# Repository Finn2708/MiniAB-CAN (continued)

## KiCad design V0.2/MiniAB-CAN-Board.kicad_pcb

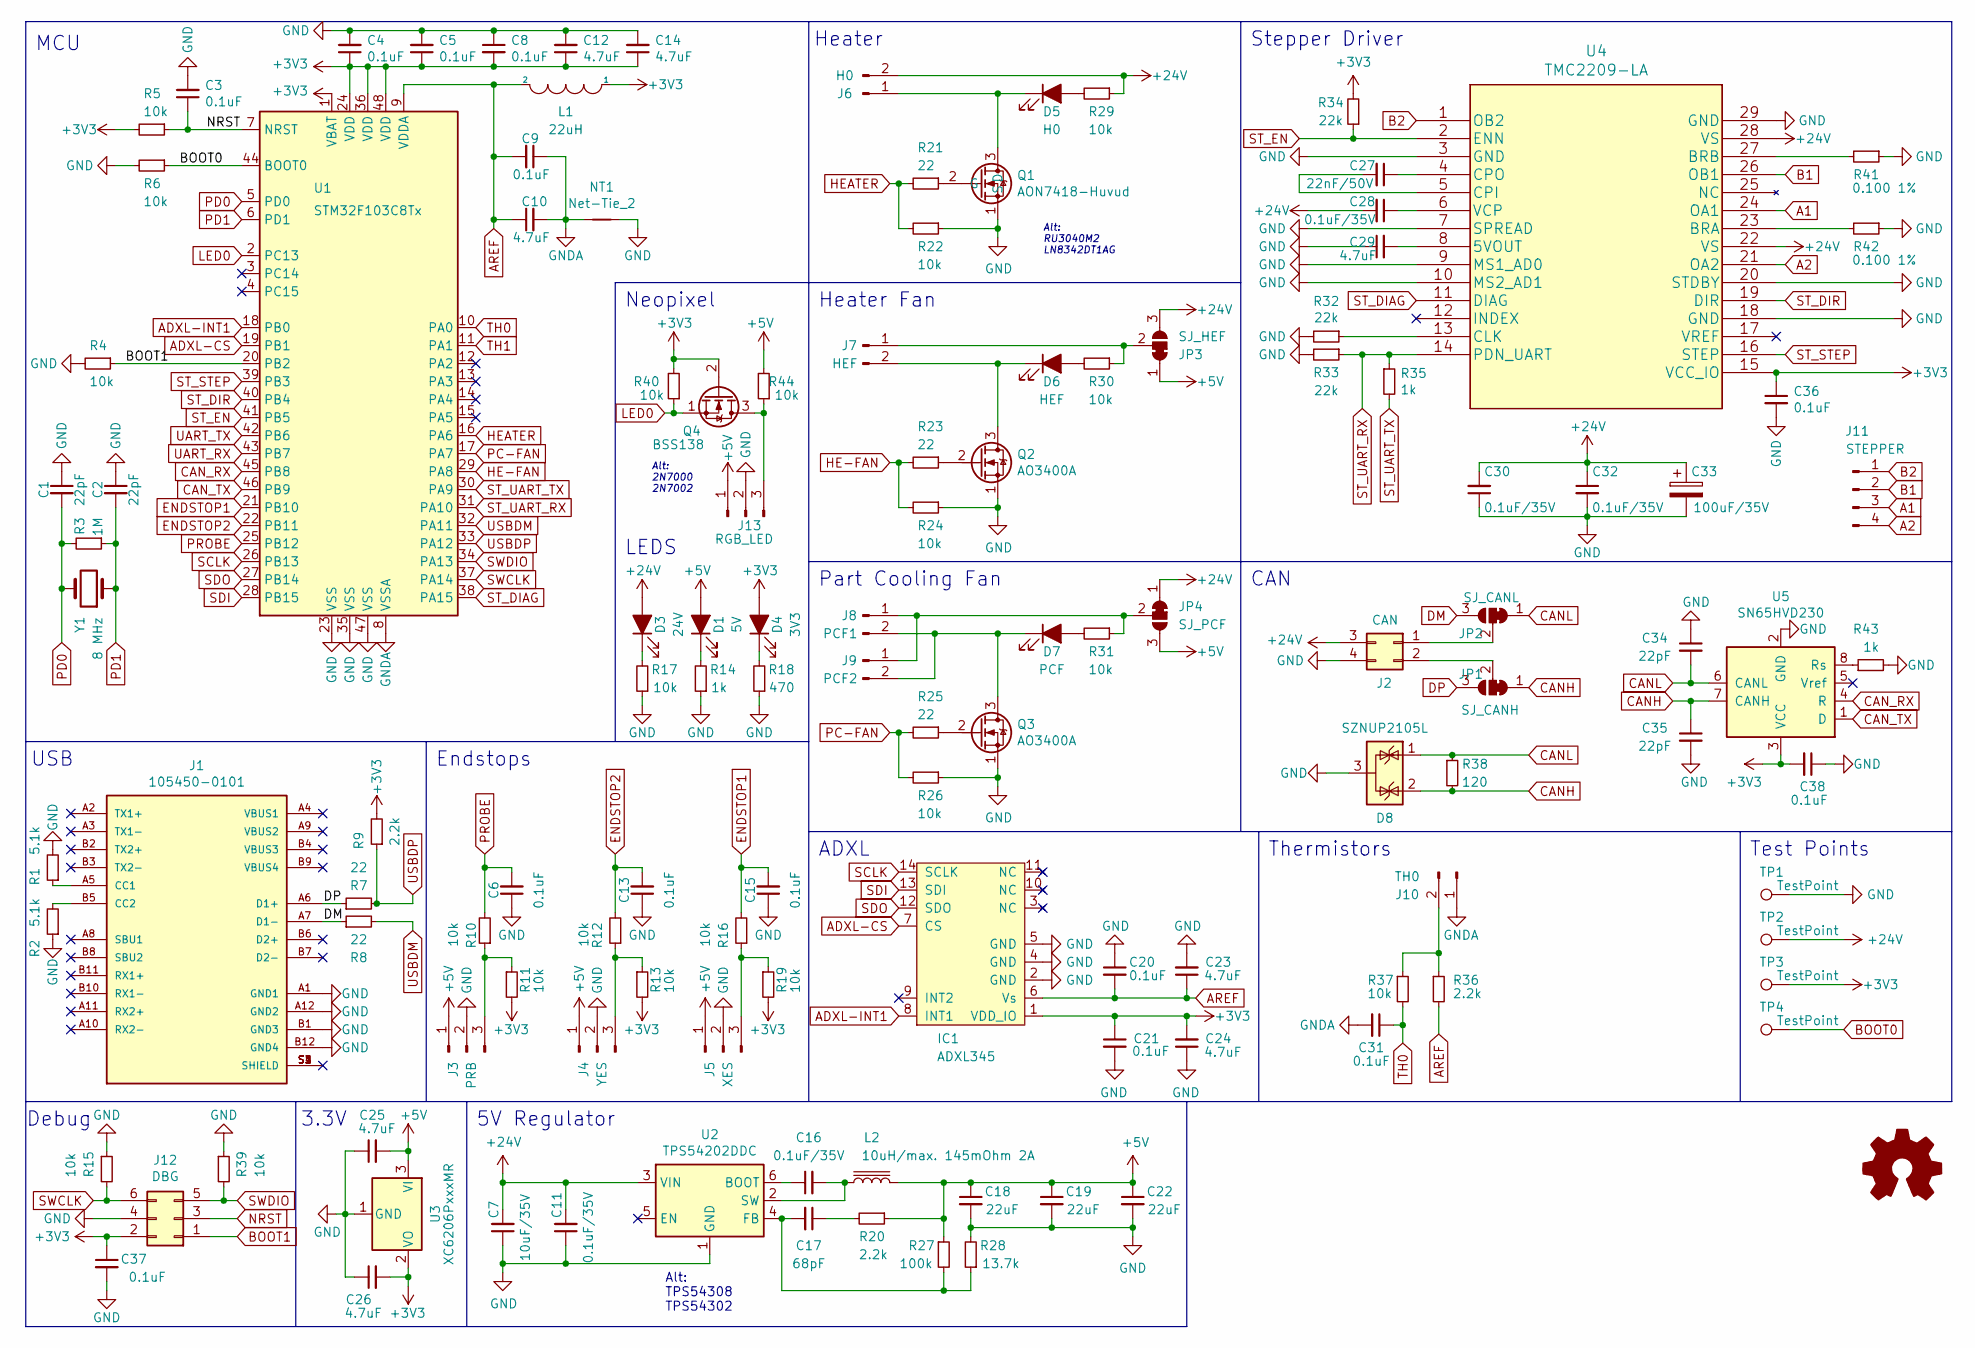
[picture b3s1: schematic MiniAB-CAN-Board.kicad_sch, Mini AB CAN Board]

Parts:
C1, C2: 22pF; C_0603_1608Metric
C3, C4, C5, C6, C8, C9, C13, C15, C20, C21, C31, C36, C37, C38: 0.1uF; C_0402_1005Metric
C7: 10uF/35V; C_1206_3216Metric
C10, C12, C14, C23, C24, C25, C26, C29: 4.7uF; C_0402_1005Metric
C11, C16, C28, C30, C32: 0.1uF/35V; C_0603_1608Metric
C17: 68pF; C_0402_1005Metric
C18, C19, C22: 22uF; C_0805_2012Metric
C27: 22nF/50V; C_0603_1608Metric
C33: 100uF/35V; CP_Elec_6.3x5.8
C34, C35: 22pF; C_0402_1005Metric
D1: 5V; LED_0402_1005Metric
D3: 24V; LED_0402_1005Metric
D4: 3V3; LED_0402_1005Metric
D5: H0; LED_0402_1005Metric
D6: HEF; LED_0402_1005Metric
D7: PCF; LED_0402_1005Metric
D8: SZNUP2105L; SOT-23
IC1: ADXL345; LGA-14_3x5mm_P0.8mm_LayoutBorder1x6y; Farnell 1853935
J1: 105450-0101; MOLEX_105450-0101
J2: CAN; Molex_Micro-Fit_3.0_43045-0400_2x02_P3.00mm_Horizontal
J3: PRB; JST_PH_B3B-PH-K_1x03_P2.00mm_Vertical
J4: YES; JST_PH_B3B-PH-K_1x03_P2.00mm_Vertical
J5: XES; JST_PH_B3B-PH-K_1x03_P2.00mm_Vertical
J6: H0; Molex_Micro-Fit_3.0_43045-0200_2x01_P3.00mm_Horizontal
J7: HEF; JST_PH_B2B-PH-K_1x02_P2.00mm_Vertical
J8: PCF1; JST_PH_B2B-PH-K_1x02_P2.00mm_Vertical
J9: PCF2; JST_PH_B2B-PH-K_1x02_P2.00mm_Vertical
J10: TH0; JST_PH_B2B-PH-K_1x02_P2.00mm_Vertical
J11: STEPPER; JST_PH_B4B-PH-K_1x04_P2.00mm_Vertical
J12: DBG; PinHeader_2x03_P1.27mm_Vertical_SMD
J13: RGB_LED; JST_PH_B3B-PH-K_1x03_P2.00mm_Vertical
JP1: SJ_CANH; SolderJumper-3_P1.3mm_Bridged2Bar12_Pad1.0x1.5mm
JP2: SJ_CANL; SolderJumper-3_P1.3mm_Bridged2Bar12_Pad1.0x1.5mm
JP3: SJ_HEF; SolderJumper-3_P1.3mm_Bridged2Bar12_Pad1.0x1.5mm
JP4: SJ_PCF; SolderJumper-3_P1.3mm_Bridged2Bar12_Pad1.0x1.5mm
L1: 22uH; L_0805_2012Metric
L2: 10uH/max. 145mOhm 2A; L_Sunlord_MWSA0518_5.4x5.2mm
NT1: Net-Tie_2; NetTie-2_SMD_Pad0.5mm
Q1: AON7418-Huvud; DFN-8-1EP_3x3mm_P0.65mm_EP1.7x2.05mm
Q2, Q3: AO3400A; SOT-23
Q4: BSS138; SOT-23
R1, R2: 5.1k; R_0402_1005Metric
R3: 1M; R_0402_1005Metric
R4, R5, R6, R10, R11, R12, R13, R15, R16, R17, R19, R22, R24, R26, R29, R30, R31, R37, R39, R40, R44: 10k; R_0402_1005Metric
R7, R8, R21, R23, R25: 22; R_0402_1005Metric
R9, R20, R36: 2.2k; R_0402_1005Metric
R14, R35, R43: 1k; R_0402_1005Metric
R18: 470; R_0402_1005Metric
R27: 100k; R_0402_1005Metric
R28: 13.7k; R_0402_1005Metric
R32, R33, R34: 22k; R_0402_1005Metric
R38: 120; R_0402_1005Metric
R41, R42: 0.100 1%; R_0402_1005Metric
TP1, TP2, TP3, TP4: TestPoint; TestPoint_Pad_D1.5mm
U1: STM32F103C8Tx; LQFP-48_7x7mm_P0.5mm
U2: TPS54202DDC; SOT-23-6
U3: XC6206PxxxMR; SOT-23
U4: TMC2209-LA
U5: SN65HVD230; SOIC-8_3.9x4.9mm_P1.27mm
Y1: 8 MHz; Crystal_SMD_5032-2Pin_5.0x3.2mm

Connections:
+3V3: C4.1, C5.1, C8.2, C12.1, C14.1, C21.1, C24.2, C26.2, C36.1, C37.1, C38.2, D4.2 (A), IC1.1 (VDD_IO), J12.2, L1.1, Q4.2 (G), R5.2, R9.2, R11.2, R13.2, R19.2, R34.2, R40.2, TP3.1, U1.1 (VBAT), U1.24 (VDD), U1.36 (VDD), U1.48 (VDD), U3.2 (VO), U4.15 (VCC_IO), U5.3 (VCC)
+5V: C18.1, C19.1, C22.1, C25.2, D1.2 (A), J3.1, J4.1, J5.1, J13.1, JP3.1 (A), JP4.3 (B), L2.2, R20.1, R27.1, R44.2, U3.3 (VI)
+24V: C7.2, C11.2, C28.2, C30.2, C32.1, C33.1, D3.2 (A), J2.3, J6.2, JP3.3 (B), JP4.1 (A), R29.1, TP2.1, U2.3 (VIN), U4.22 (VS), U4.28 (VS)
A1: J11.3, U4.24 (OA1)
A2: J11.4, U4.21 (OA2)
ADXL-CS: IC1.7 (CS), U1.19 (PB1)
ADXL-INT1: IC1.8 (INT1), U1.18 (PB0)
AREF: C9.2, C10.1, C20.2, C23.1, IC1.6 (Vs), L1.2, R36.2, U1.9 (VDDA)
B1: J11.2, U4.26 (OB1)
B2: J11.1, U4.1 (OB2)
BOOT0: R6.1, TP4.1, U1.44 (BOOT0)
BOOT1: J12.1, R4.1, U1.20 (PB2)
CANH: C35.1, D8.2 (K), JP1.1 (A), R38.2, U5.7 (CANH)
CANL: C34.2, D8.1 (K), JP2.1 (A), R38.1, U5.6 (CANL)
CAN_RX: U1.45 (PB8), U5.4 (R)
CAN_TX: U1.46 (PB9), U5.1 (D)
DM: J1.A7 (D1-), JP2.3 (B), R8.1
DP: J1.A6 (D1+), JP1.3 (B), R7.1
ENDSTOP1: C15.2, R16.2, U1.21 (PB10)
ENDSTOP2: C13.2, R12.2, U1.22 (PB11)
GND: C1.1, C2.1, C3.2, C4.2, C5.2, C6.1, C7.1, C8.1, C11.1, C12.2, C13.1, C14.2, C15.1, C18.2, C19.2, C20.1, C21.2, C22.2, C23.2, C24.1, C25.1, C26.1, C29.1, C30.1, C32.2, C33.2, C34.1, C35.2, C36.2, C37.2, C38.1, D8.3 (A), IC1.2 (GND), IC1.4 (GND), IC1.5 (GND), J1.A1 (GND1), J1.A12 (GND2), J1.B1 (GND3), J1.B12 (GND4), J2.4, J3.2, J4.2, J5.2, J12.4, J13.2, NT1.2, Q1.1 (S), Q2.1 (S), Q3.1 (S), R1.2, R2.1, R4.2, R6.2, R14.1, R15.1, R17.1, R18.1, R22.1, R24.1, R26.1, R28.2, R32.2, R33.2, R39.1, R41.1, R42.1, R43.2, TP1.1, U1.23 (VSS), U1.35 (VSS), U1.47 (VSS), U2.1 (GND), U3.1 (GND), U4.3 (GND), U4.7 (SPREAD), U4.9 (MS1_AD0), U4.10 (MS2_AD1), U4.18 (GND), U4.20 (STDBY), U4.29 (GND), U5.2 (GND)
GNDA: C9.1, C10.2, C31.2, J10.1, NT1.1, U1.8 (VSSA)
HE-FAN: R23.2, R24.2, U1.29 (PA8)
HEATER: R21.2, R22.2, U1.16 (PA6)
LED0: Q4.1 (S), R40.1, U1.2 (PC13)
NRST: C3.1, J12.3, R5.1, U1.7 (NRST)
unnamed: C16.1, U2.6 (BOOT)
unnamed: C16.2, L2.1, U2.2 (SW)
unnamed: C17.1, R20.2
unnamed: C17.2, R27.2, R28.1, U2.4 (FB)
unnamed: C27.1, U4.4 (CPO)
unnamed: C27.2, U4.5 (CPI)
unnamed: C28.1, U4.6 (VCP)
unnamed: C29.2, U4.8 (5VOUT)
unnamed: D1.1 (K), R14.2
unnamed: D3.1 (K), R17.2
unnamed: D4.1 (K), R18.2
unnamed: D5.1 (K), J6.1, Q1.3 (D)
unnamed: D5.2 (A), R29.2
unnamed: D6.1 (K), J7.2, Q2.3 (D)
unnamed: D6.2 (A), R30.2
unnamed: D7.1 (K), J8.2, J9.2, Q3.3 (D)
unnamed: D7.2 (A), R31.2
unnamed: J1.A5 (CC1), R1.1
unnamed: J1.B5 (CC2), R2.2
unnamed: J1.S1 (SHIELD), J1.S2 (SHIELD), J1.S3 (SHIELD), J1.S4 (SHIELD)
unnamed: J2.1, JP2.2 (C)
unnamed: J2.2, JP1.2 (C)
unnamed: J3.3, R10.1, R11.1
unnamed: J4.3, R12.1, R13.1
unnamed: J5.3, R16.1, R19.1
unnamed: J7.1, JP3.2 (C), R30.1
unnamed: J8.1, J9.1, JP4.2 (C), R31.1
unnamed: J10.2, R36.1, R37.1
unnamed: J13.3, Q4.3 (D), R44.1
unnamed: Q1.2 (G), R21.1
unnamed: Q2.2 (G), R23.1
unnamed: Q3.2 (G), R25.1
unnamed: R32.1, U4.13 (CLK)
unnamed: R41.2, U4.27 (BRB)
unnamed: R42.2, U4.23 (BRA)
unnamed: R43.1, U5.8 (Rs)
PC-FAN: R25.2, R26.2, U1.17 (PA7)
PD0: C1.2, R3.2, U1.5 (PD0), Y1.2
PD1: C2.2, R3.1, U1.6 (PD1), Y1.1
PROBE: C6.2, R10.2, U1.25 (PB12)
SCLK: IC1.14 (SCLK), U1.26 (PB13)
SDI: IC1.13 (SDI), U1.28 (PB15)
SDO: IC1.12 (SDO), U1.27 (PB14)
ST_DIAG: U1.38 (PA15), U4.11 (DIAG)
ST_DIR: U1.40 (PB4), U4.19 (DIR)
ST_EN: R34.1, U1.41 (PB5), U4.2 (ENN)
ST_STEP: U1.39 (PB3), U4.16 (STEP)
ST_UART_RX: R33.1, R35.1, U1.31 (PA10), U4.14 (PDN_UART)
ST_UART_TX: R35.2, U1.30 (PA9)
SWCLK: J12.6, R15.2, U1.37 (PA14)
SWDIO: J12.5, R39.2, U1.34 (PA13)
TH0: C31.1, R37.2, U1.10 (PA0)
USBDM: R8.2, U1.32 (PA11)
USBDP: R7.2, R9.1, U1.33 (PA12)

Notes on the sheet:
Test Points
Part Cooling Fan
USB
3.3V
ADXL
Thermistors
Alt: 2N7000 2N7002
LEDS
Alt: TPS54308 TPS54302
CAN
Neopixel
Endstops
MCU
Heater
5V Regulator
Alt: RU3040M2 LN8342DT1AG
Debug
Stepper Driver
Heater Fan

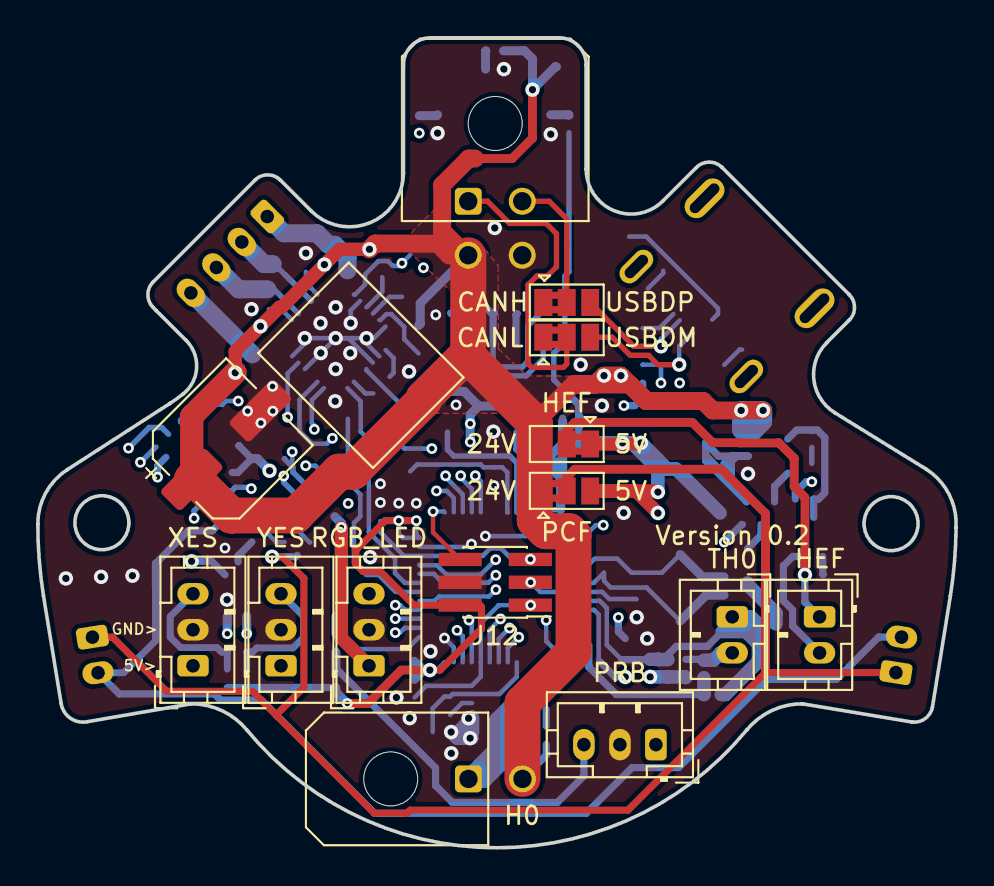
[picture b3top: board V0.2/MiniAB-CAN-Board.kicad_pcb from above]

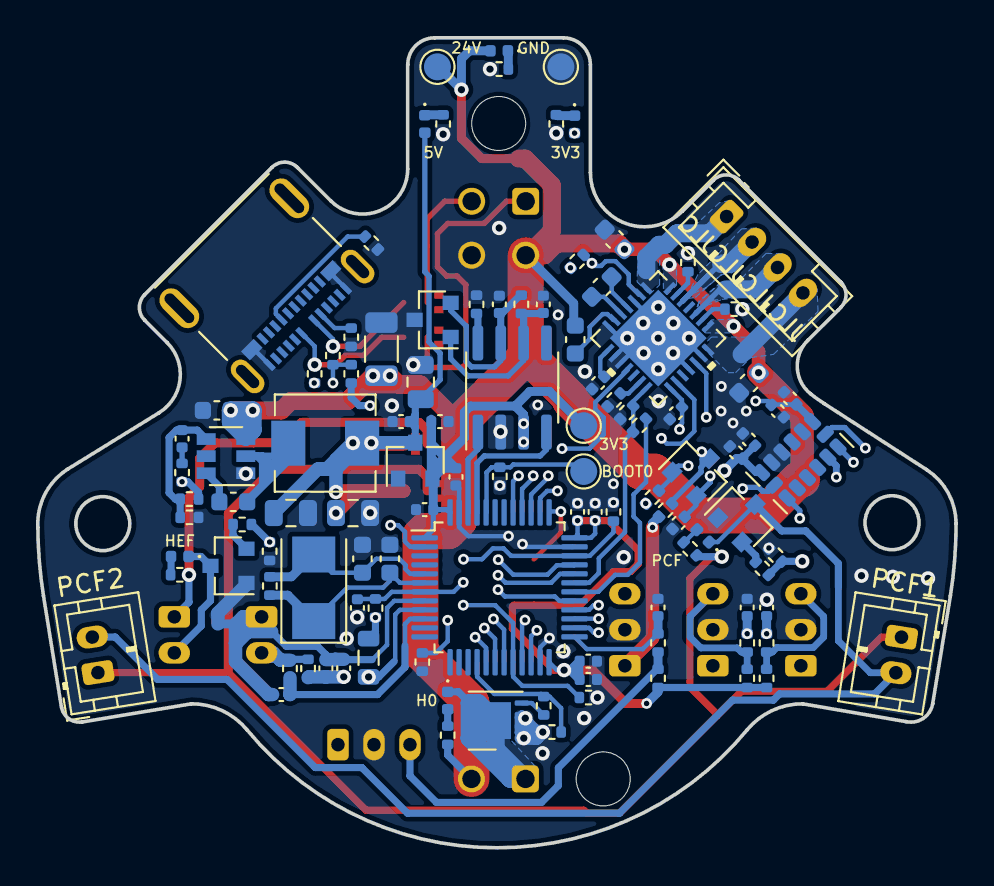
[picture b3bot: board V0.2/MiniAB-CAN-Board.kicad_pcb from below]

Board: 4 copper layers, 51.0 x 45.0 mm, 124 parts (110 on the bottom side), 80 nets.

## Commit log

2021-11-29 Fix library imports
2021-12-02 Add exposed copper pad for heat sink
2021-12-02 Heatsink oriented at 45deg because 24V conflict
2021-12-12 Add BOM
2021-12-12 Updates to PCB
2021-12-14 add debug port and rework of schematic
2021-12-14 Add 3 Pin Endstops + LED Port
2021-12-15 change rgb led pin order, some rearrangements
2021-12-20 add missing footprints
2021-12-26 Add preliminary V0.2
2021-12-30 add gitignore to ignore autosave and backup files
2021-12-30 complete routing, repair zones, review back side
2021-12-31 Add TMC2209 to V0.3 Schematic
2021-12-31 Add STM32 and ADXL to V0.3 Schematic
2022-01-02 Update V0.3 schematic
2022-01-02 Chrystal Design done
2022-01-03 PCB Layout V0.3 WIP
2022-01-03 Updated footprints to 0402 if possible
2022-01-04 TMC added to V0.3
2022-01-04 Finished Front Side
2022-01-04 Remove random files
2022-01-04 Revert "Remove random files"
    This reverts commit 93dff4540d7a9e75a7fbc8ac9752cb90a1551b6a.
2022-01-04 Fix merge issues
2022-01-04 Update Fan Mosfet Placement
2022-01-04 Stuck on connector placement
2022-01-05 Start new experimental design
2022-01-06 Add THT JST version with new DCDC converter
2022-01-06 Update PCB
2022-01-06 Update DCDC Section
2022-01-08 V0.4 finished
2022-01-08 Fix GND connection on TCAN330
2022-01-08 Add silkscreen annotations
2022-01-08 Add step models for CAD export
2022-01-08 Update Step model
2022-01-09 Add gerbers
2022-01-14 Fix minor issues on schematic, pcb still pending
2022-02-04 add polarity check, change crystal, change debug, add buttons, exchange 5V regulator, correct MOSFETs, updated TMC2209 and all capacitors
2022-02-06 reduces CAN interface, complets USB interface, add new mounting holes
2022-02-13 Add single sided version
2022-02-17 JNP Layout and first routings
2022-02-17 Routing finished
2022-02-17 Add vias to board edge
2022-02-17 Update routing
2022-02-22 Update silk screen
2022-02-24 Update silkscreen
2022-02-27 Update BOM
2022-05-19 Add pinout
2022-05-19 Add thermal images
2022-05-19 Add interactive BOM
2022-05-19 Fix iBOM
2022-05-19 Add license
2022-05-19 Add featuresto README
2022-05-19 Fix iBOM link
    Fix ibom link
    Fix iBOM link
    Fix iBOM link
    Fix iBOM link
    Fix iBOM link
    Fix iBOM link
